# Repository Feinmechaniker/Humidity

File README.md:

# Humidity-Controller
Humidity-Control, basierend auf einem ESP8266, bestimmt die Temperatur und die relative Luftfeuchtigkeit im Innen- und Außenbereich. Aus diesen Messdaten wird jede Minute für den Innen- und Außenbereich jeweils die absolute Luftfeuchtigkeit in g/m³ berechnet. In Abhängigkeit einer dynamischen Hystereseschwelle kann über ein Relais ein Lüfter angesteuert werden. Liegt die absolute Feuchte im Innenraum über der absoluten Feuchte im Außenbereich und ist die minimale Außentemperatur noch nicht erreicht, wird der Lüfter eingeschaltet. Die Hysterese wird automatisch dynamisch über die minimale Außentemperatur und die Genauigkeit der Feuchtesensoren berechnet. 
Das Zusamenspiel der einzelnen Komponenten zeigt die nachfolgende Abbildung.

Optional können auf einem OLED-Display die aktuellen Temperaturen und die absoluten Feuchten abgelesen werden.

## Dashboard lokal
Ein Dashboard auf einem lokalen Webserver des Controllers ermöglich Abfrage bzw. Änderung
- des Schaltzustandes des Lüfters
- der minimalen Schalttemperatur
- der Temperaturen im Innen- und Außenbereich
- der relativen und absoluten Luftfeuchtigkeiten im Innen- und Außenbereich

## Dashboard Grafana
Bei Bedarf werden sowohl die Messdaten als auch die daraus berechneten Ergebnisse über MQTT an eine Datenbank gesendet. Diese können dann über eine grafische Visualisierung wie z.B. Grafana dargestellt werden. 

(c) 2022 Joe.G

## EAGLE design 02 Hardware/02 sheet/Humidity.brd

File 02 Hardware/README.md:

# Humidity-Controller
Die Hardware besteht aus einem NodeMCU Lua Amica Modul V2 ESP8266 Board, einem Netzteil und einer Relaisschaltung, welche über einen Optokoppler von der DC-Seite getrennt ist. Die Leiterplatte befindet sich in einem Z108 Hutschienengehäuse.  

Leiterplatten können unter:
https://aisler.net/p/RMIZEMKT
bezogen werden.

(c) 2022 Joe.G

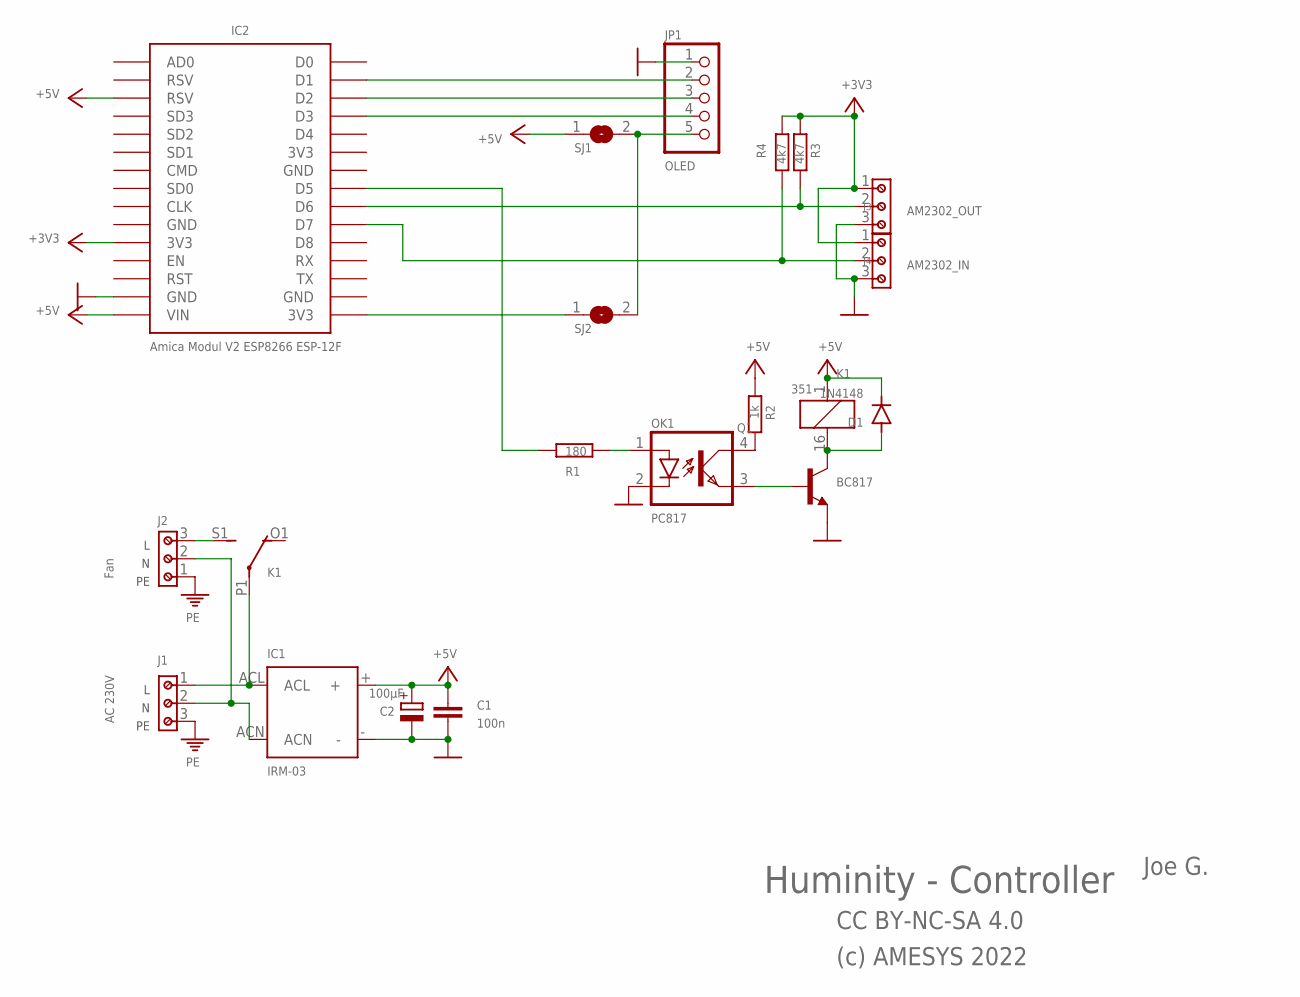
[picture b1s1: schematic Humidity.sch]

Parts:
C1: 100n; C1206
C2: 100µF; SMC_C
D1: 1N4148; SOD123
IC1: IRM-03
IC2: Amica Modul V2 ESP8266 ESP-12F; ESP12E_DEVKIT
J1: AC 230V; 691216910003
J2: Fan; 691216910003
J3: AM2302_OUT; 691216710003
J4: AM2302_IN; 691216710003
JP1: OLED; 1X05
K1: 351
OK1: PC817; DIL04
Q1: BC817; TRANSISTOR-NPN_SOT23-BEC
R1: 180; R1206
R2: 1k; M1206
R3, R4: 4k7; M1206
SJ1, SJ2: SJ

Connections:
+3V3: IC2.3V3@0 (3V3), J3.1, J4.1, R3.1, R4.1
+5V: C1.1, C2.+, D1.C, IC1.+, IC2.RSV@1 (RSV), IC2.VIN, K1.1, R2.1, SJ1.1
GND: C1.2, C2.-, IC1.-, IC2.GND@1 (GND), J3.3, J4.3, JP1.1, OK1.2 (C), Q1.E
unnamed: IC2.D6, J3.2, R3.2
unnamed: IC2.D7, J4.2, R4.2
unnamed: JP1.5, SJ1.2, SJ2.2
unnamed: IC1.ACL, J1.1, K1.P1
unnamed: IC1.ACN, J1.2, J2.2
unnamed: OK1.1 (A), R1.2
unnamed: OK1.4 (COL), R2.2
unnamed: D1.A, K1.16 (2), Q1.C
unnamed: OK1.3 (EMIT), Q1.B
unnamed: J2.3, K1.S1 (S)
unnamed: IC2.D1, JP1.2
unnamed: IC2.D2, JP1.3
unnamed: IC2.D3, JP1.4
unnamed: IC2.3V3@2 (3V3), SJ2.1
PE: J1.3, J2.1
REL: IC2.D5, R1.1

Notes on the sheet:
Huminity - Controller
CC BY-NC-SA 4.0
(c) AMESYS 2022
Joe G.

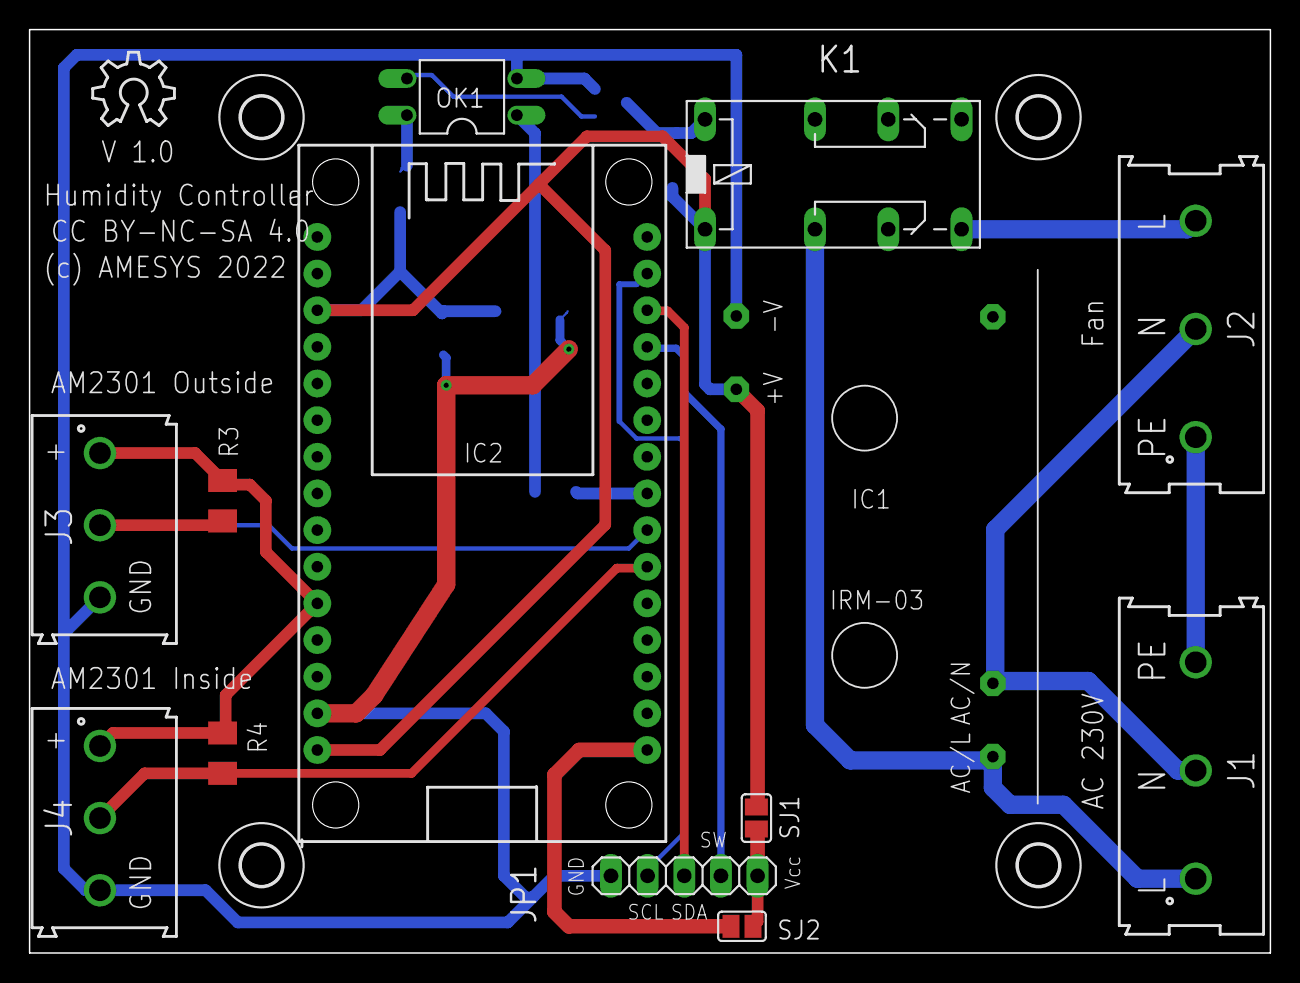
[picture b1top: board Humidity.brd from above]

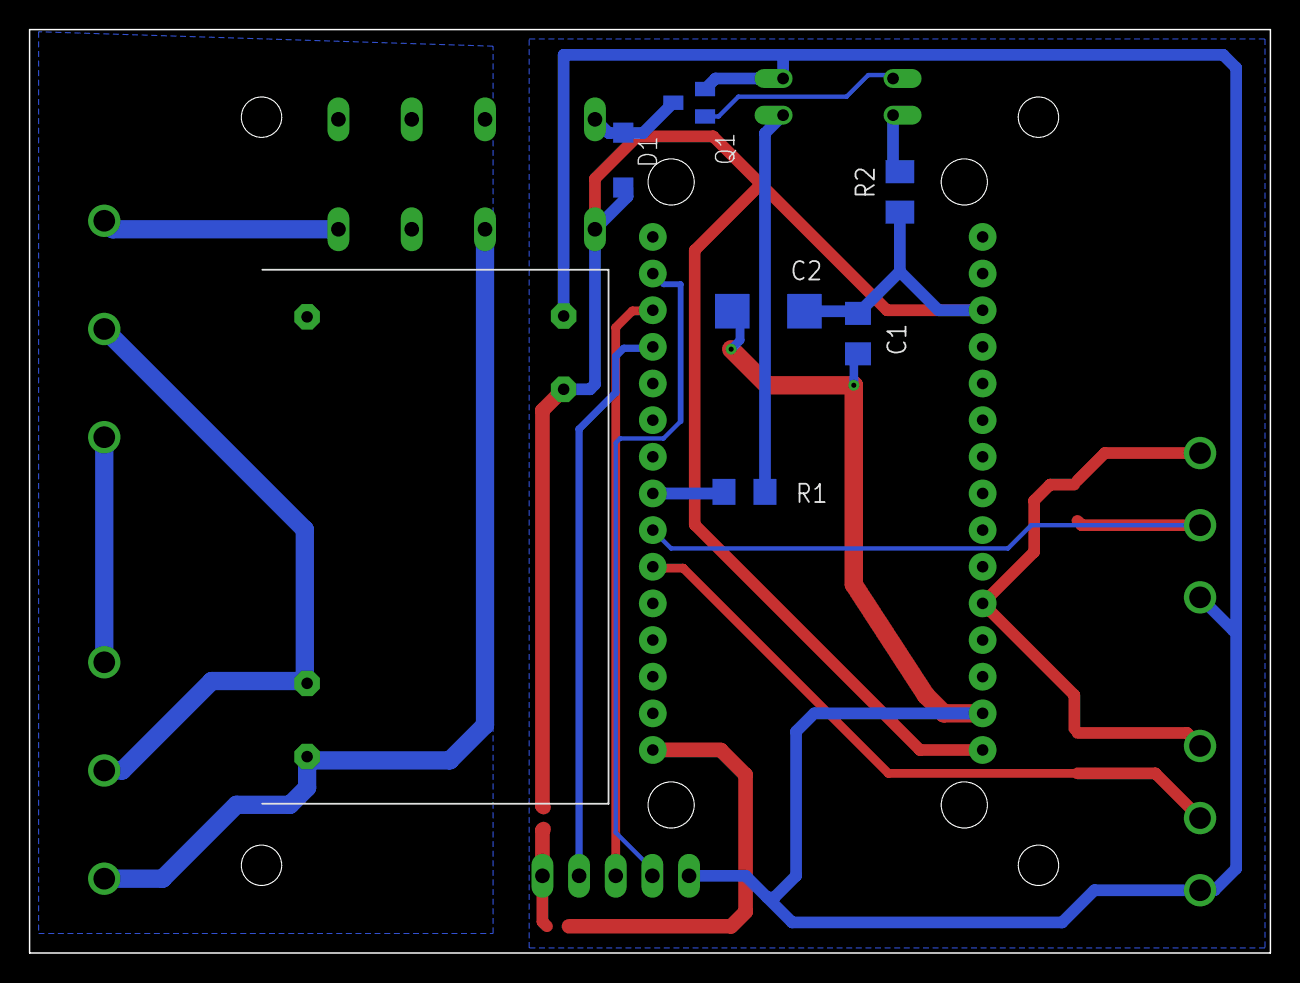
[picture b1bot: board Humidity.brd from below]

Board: 2 copper layers, 86.0 x 64.0 mm, 24 parts (6 on the bottom side), 19 nets.

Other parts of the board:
U$1, U$3, U$4, U$5: 2,8
U$7: OSHW_8X200_NOTEXT

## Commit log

2022-11-23 LÖSCHEN
2022-11-24 24.11.2022
2022-11-24 09:30
2022-11-24 Website
2022-11-25 25.11.22
2022-11-27 Data over MQTT
2022-11-27 MQTT
2022-12-02 2% Hysterese
2022-12-08 Berechnung Taupunkt
2022-12-08 new config.dat
2022-12-09 Erweiterungen für Grafana Dashboard
2022-12-10 with AMICA Package
2022-12-19 Grafana Dashboard
2022-12-19 Beschreibung Hardware
2022-12-19 Überblick
2022-12-19 Hardware
2022-12-19 Dugfix Boarddesign
2022-12-19 Board Design
2022-12-19 MathCad Berechnung
2022-12-19 ESPEasy
2022-12-19 Übersichtsdarstellung
2022-12-19 readme
2022-12-19 Schaltung

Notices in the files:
parts and their libraries:
Eagle_WR-TBL Rising Cage Clamp: Copyright: Würth Elektronik
